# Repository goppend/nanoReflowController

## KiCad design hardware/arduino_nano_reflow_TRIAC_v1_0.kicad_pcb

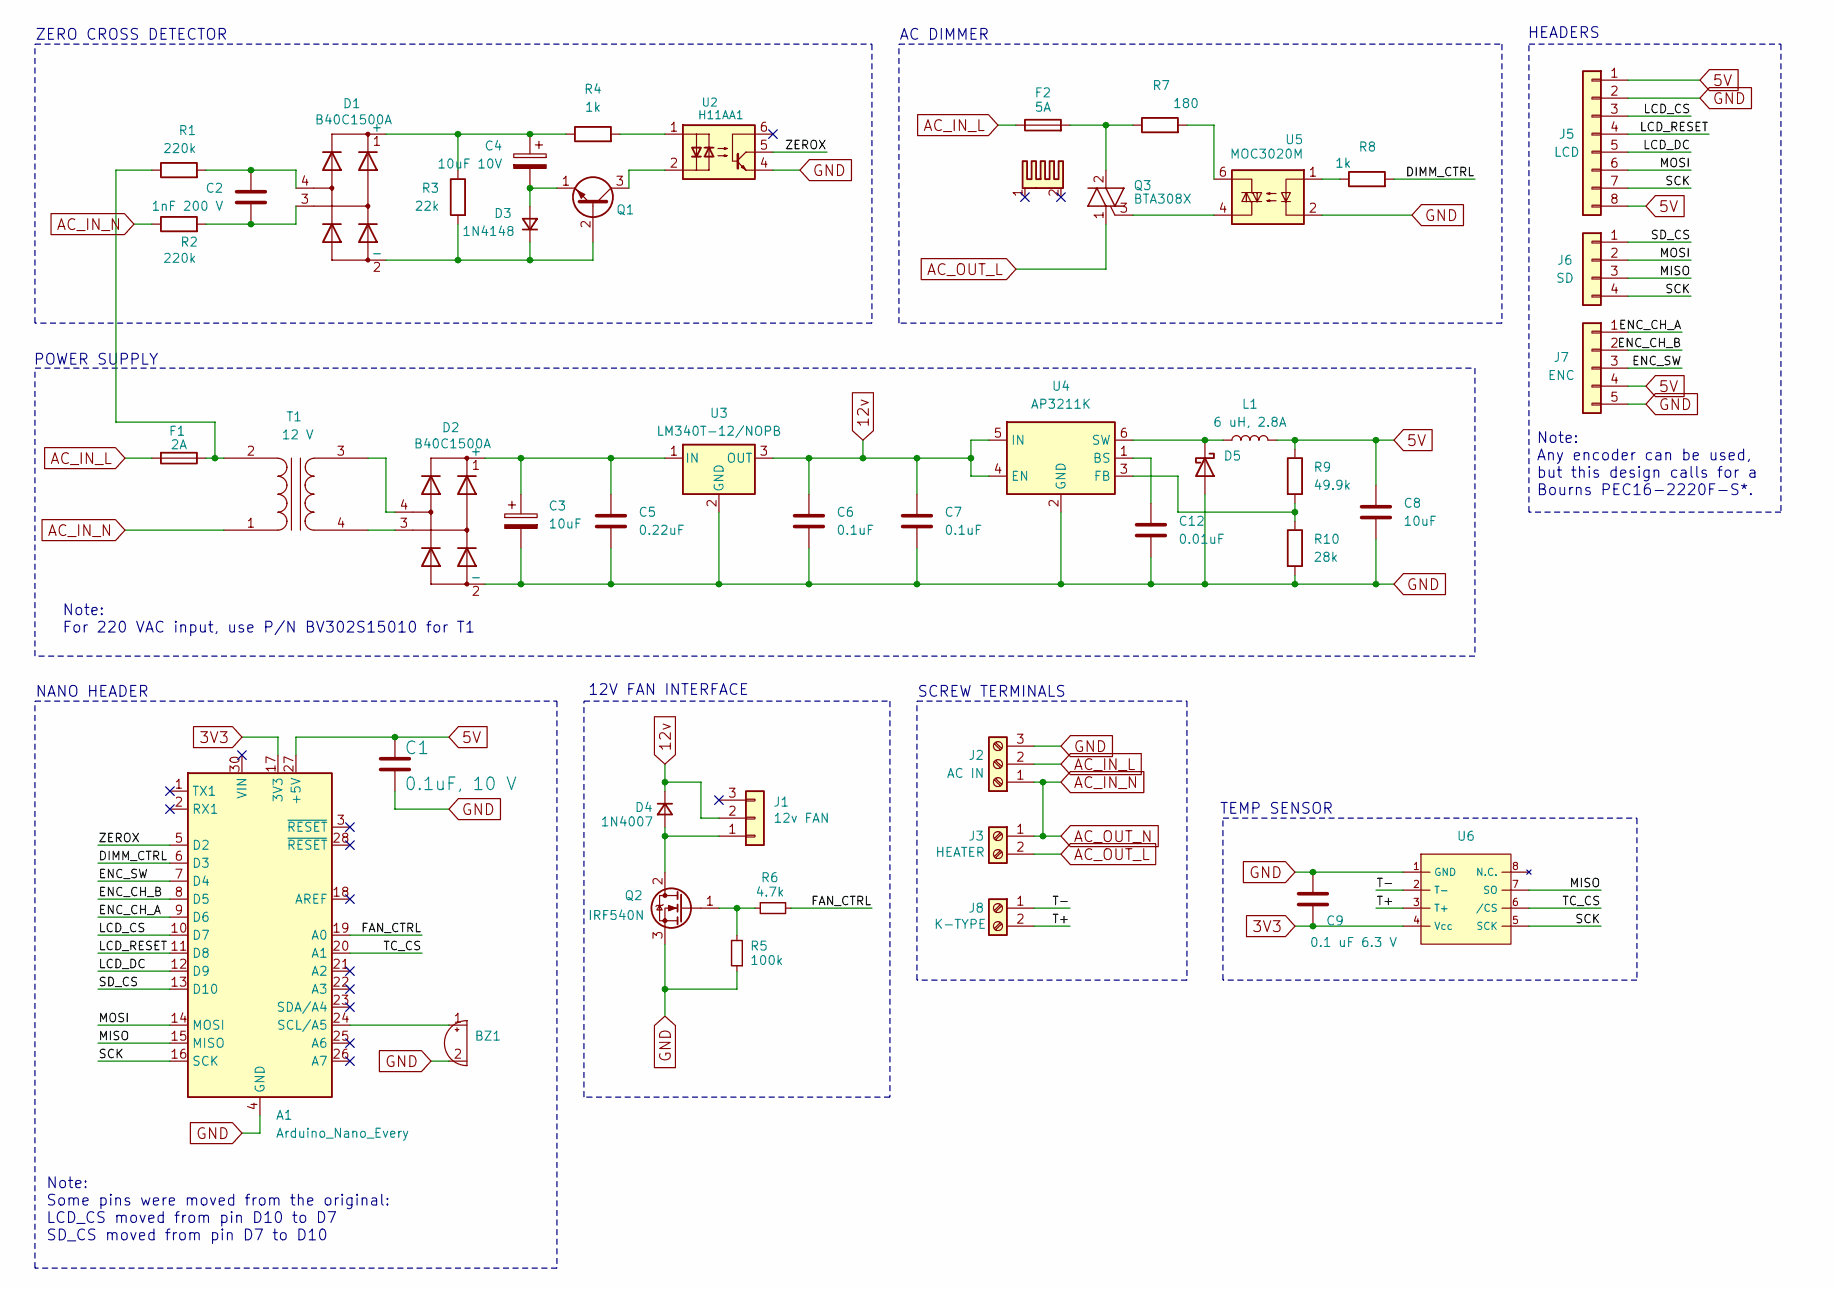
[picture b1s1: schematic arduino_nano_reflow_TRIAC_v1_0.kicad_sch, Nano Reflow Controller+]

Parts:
A1: Arduino_Nano_Every; Arduino_Nano
BZ1: Buzzer_TDK_PS1240P02BT_D12.2mm_H6.5mm; Part Number WT-1205
C1: 0.1uF, 10 V; C_0805_2012Metric_Pad1.18x1.45mm_HandSolder; Part Number C0805C104K8RACTU
C2: 1nF 200 V; C_Rect_L7.2mm_W2.5mm_P5.00mm_FKS2_FKP2_MKS2_MKP2; Part Number R82MC1100DQ50K
C3: 10uF; CP_Radial_D5.0mm_P2.00mm; Part Number ESS106M025AB2AA
C4: 10uF 10V; CP_Radial_D5.0mm_P2.00mm; Part Number ESK106M010AC3AA
C5: 0.22uF; C_0805_2012Metric_Pad1.18x1.45mm_HandSolder; Part Number C0805C224MMREC7210
C6, C7: 0.1uF; C_0805_2012Metric_Pad1.18x1.45mm_HandSolder; Part Number C0805C104K3RACTU
C8: 10uF; C_0805_2012Metric_Pad1.18x1.45mm_HandSolder; Part Number C0805C106K9PACTU
C9: 0.1 uF 6.3 V; C_0805_2012Metric_Pad1.18x1.45mm_HandSolder; Part Number C0805C104K9RACTU
C12: 0.01uF; C_0805_2012Metric_Pad1.18x1.45mm_HandSolder; Part Number C0805C103K8RACTU
D1, D2: B40C1500A; B40C; Part Number B40C1500A
D3: 1N4148; D_DO-35_SOD27_P7.62mm_Horizontal; Part Number 1N4148
D4: 1N4007; D_DO-35_SOD27_P7.62mm_Horizontal; Part Number 1N4007
D5: 40V, 2A; D_SMA_Handsoldering; Part Number B240A-13-F
F1: 2A; FUSE_0PTF0078P_LTF; Part Number 0PTF0078P
F2: 5A; FUSE_0PTF0078P_LTF; Part Number 0PTF0078P
HS1: Aavid 51300 Heatsink; Part Number 513102B02500G
J1: 12v FAN; FanPinHeader_1x03_P2.54mm_Vertical; Part Number 640456-3
J2: AC IN; TerminalBlock_Phoenix_MKDS-1,5-3_1x03_P5.00mm_Horizontal; Part Number 1727023
J3: HEATER; TerminalBlock_Phoenix_MKDS-1,5-2_1x02_P5.00mm_Horizontal; Part Number 1727010
J5: LCD; PinHeader_1x08_P2.54mm_Vertical; Part Number M20-9990846
J6: SD; PinHeader_1x04_P2.54mm_Vertical; Part Number M20-9990546
J7: ENC; PinHeader_1x05_P2.54mm_Vertical; Part Number M20-9990546
J8: K-TYPE; TerminalBlock_Phoenix_MKDS-1,5-2_1x02_P5.00mm_Horizontal; Part Number 1727010
L1: 6 uH, 2.8A; Bourns SRN6028C Inductor hand solder; Part Number SRN6028C-6R0M
Q1: 40V, 0.8A; TO-92_Inline_Wide; Part Number PN2222A PBFREE
Q2: IRF540N; TO-220-3_Vertical; Part Number IRF540N
Q3: BTA308X; TO-220-3_Vertical; Part Number BTA308X
R1, R2: 220k; R_Axial_DIN0204_L3.6mm_D1.6mm_P5.08mm_Horizontal; Part Number CF18JT220K
R3: 22k; R_Axial_DIN0204_L3.6mm_D1.6mm_P5.08mm_Horizontal; Part Number CF18JT22K0
R4, R8: 1k; R_Axial_DIN0204_L3.6mm_D1.6mm_P5.08mm_Horizontal; Part Number CF18JT1K00
R5: 100k; R_Axial_DIN0204_L3.6mm_D1.6mm_P5.08mm_Horizontal; Part Number CF18JT100K
R6: 4.7k; R_Axial_DIN0204_L3.6mm_D1.6mm_P5.08mm_Horizontal; Part Number CF18JT4K70
R7: 180; R_Axial_DIN0207_L6.3mm_D2.5mm_P7.62mm_Horizontal; Part Number CF18JT180R
R9: 49.9k; R_0805_2012Metric_Pad1.20x1.40mm_HandSolder; Part Number RK73H2ATTD4992F
R10: 28k; R_0805_2012Metric_Pad1.20x1.40mm_HandSolder; Part Number RK73H2ATTD2802F
T1: 12 V; BV301S15010; Part Number BV301S15010
U2: H11AA1; DIP-6_W7.62mm; Part Number H11AA1
U3: LM340T-12/NOPB; TO-263-3_TabPin4; Part Number LM340T-12/NOPB
U4: AP3211K; SOT-23-6_Handsoldering; Part Number AP3211K
U5: MOC3020M; DIP-6_W7.62mm_Socket_LongPads; Part Number MOC3020M
U6: SO-8_3.9x4.9mm_P1.27mm; Part Number MAX6675

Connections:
3V3: A1.17 (3V3), C9.2, U6.4 (Vcc)
5V: A1.27 (+5V), C1.1, C8.1, J5.1, J5.8, J7.4, L1.2, R9.1
12v: C6.1, C7.1, D4.1 (K), J1.2, U3.3 (OUT), U4.4 (EN), U4.5 (IN)
/DIMM_CTRL: A1.6 (D3), R8.2
/ENC_CH_A: A1.9 (D6), J7.1
/ENC_CH_B: A1.8 (D5), J7.2
/ENC_SW: A1.7 (D4), J7.3
/FAN_CTRL: A1.19 (A0), R6.1
/LCD_CS: A1.10 (D7), J5.3
/LCD_DC: A1.12 (D9), J5.5
/LCD_RESET: A1.11 (D8), J5.4
/MISO: A1.15 (MISO), J6.3, U6.7 (SO)
/MOSI: A1.14 (MOSI), J5.6, J6.2
/SCK: A1.16 (SCK), J5.7, J6.4, U6.5 (SCK)
/SD_CS: A1.13 (D10), J6.1
/T+: J8.2, U6.3 (T+)
/T-: J8.1, U6.2 (T-)
/TC_CS: A1.20 (A1), U6.6 (/CS)
/ZEROX: A1.5 (D2), U2.5
AC_IN_L: F1.2, F2.1, J2.2
AC_IN_N: J2.1, J3.1, R2.1, T1.1 (AA)
AC_OUT_L: J3.2, Q3.1 (A1)
GND: A1.4 (GND), A1.29 (GND), BZ1.2 (+), C1.2, C3.2, C5.2, C6.2, C7.2, C8.2, C9.1, C12.2, D2.2 (-), D5.2 (A), J2.3, J5.2, J7.5, Q2.3 (S), R5.1, R10.2, U2.4, U3.2 (GND), U4.2 (GND), U5.2, U6.1 (GND)
unnamed: A1.24 (SCL/A5), BZ1.1 (-)
unnamed: C2.1, D1.4, R1.2
unnamed: C2.2, D1.3, R2.2
unnamed: C4.1, D1.1 (+), R3.1, R4.1
unnamed: D1.2 (-), D3.1 (K), Q1.2 (B), R3.2
unnamed: C3.1, C5.1, D2.1 (+), U3.1 (IN)
unnamed: C4.2, D3.2 (A), Q1.1 (E)
unnamed: D4.2 (A), J1.1, Q2.2 (D)
unnamed: D5.1 (K), L1.1, U4.6 (SW)
unnamed: Q1.3 (C), U2.2
unnamed: Q2.1 (G), R5.2, R6.2
unnamed: F2.2, Q3.2 (A2), R7.1
unnamed: Q3.3 (G), U5.4
unnamed: R4.2, U2.1
unnamed: R7.2, U5.6
unnamed: R8.1, U5.1
unnamed: F1.1, R1.1, T1.2 (AB)
unnamed: D2.4, T1.3 (SA)
unnamed: D2.3, T1.4 (SB)
unnamed: C12.1, U4.1 (BS)
unnamed: R9.2, R10.1, U4.3 (FB)

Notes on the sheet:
AC DIMMER
ZERO CROSS DETECTOR
Note: Any encoder can be used, but this design calls for a Bourns PEC16-2220F-S*.
HEADERS
Note: Some pins were moved from the original: LCD_CS moved from pin D10 to D7 SD_CS moved from pin D7 to D10
SCREW TERMINALS
TEMP SENSOR
Note: For 220 VAC input, use P/N BV302S15010 for T1
POWER SUPPLY
NANO HEADER
12V FAN INTERFACE

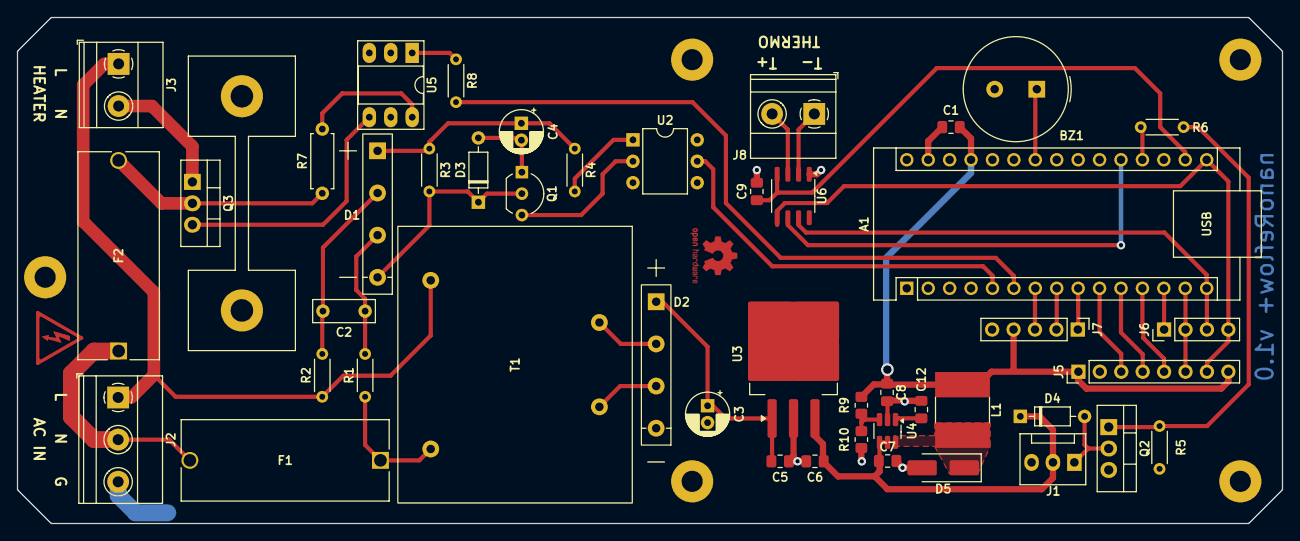
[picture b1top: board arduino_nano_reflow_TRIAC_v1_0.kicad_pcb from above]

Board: 2 copper layers, 150.0 x 60.0 mm, 47 parts (0 on the bottom side), 44 nets.

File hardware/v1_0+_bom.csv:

#,Reference,Qty,Description,Value,Manufacturer,Part Number
1,BZ1,1,Buzzer,,Same Sky,CEM-1205-IC
2,C1,1,Ceramic Capacitor,"0.1uF, 10 V",Kemet,C0805C104K8RACTU
3,C2,1,Poly Film Capacitor,1nF 200 V,Kemet,R82MC1100DQ50K
4,C3,1,Aluminum Electrolytic Capacitor,10uF,Kemet,ESS106M025AB2AA
5,C4,1,Aluminum Electrolytic Capacitor,10uF 10V,Kemet,ESK106M010AC3AA
6,C5,1,Ceramic Capacitor,0.22uF,Kemet,C0805C224MMREC7210
7,C6,1,Ceramic Capacitor,0.1uF,Kemet,C0805C104K3RACTU
8,C7,1,Ceramic Capacitor,0.1uF,Kemet,C0805C104K3RACTU
9,C8,1,Ceramic Capacitor,10uF,Kemet,C0805C106K9PACTU
10,C9,1,Ceramic Capacitor,0.1 uF 6.3 V,Kemet,C0805C104K9RACTU
11,C12,1,Ceramic Capacitor,0.01uF,Kemet,C0805C103K8RACTU
12,D1,1,Bridge Rectifier,B40C1500A,Diotec,B40C1500A
13,D2,1,Bridge Rectifier,B40C1500A,Diotec,B40C1500A
14,D3,1,"Diode, signal",1N4148,ON Semi,1N4148
15,D4,1,"Diode, rectifier",1N4007,Diotec,1N4007
16,D5,1,Schottky diode,"40V, 2A",Diodes Inc,B240A-13-F
17,F1,1,Fuse Holder,2A,Littelfuse,0PTF0078P
18,F2,1,Fuse Holder,5A,Littelfuse,0PTF0078P
19,HS1,1,Heatsink,,Bivar/Aavid,513102B02500G
20,J1,1,Fan Header,12v FAN,TE Connectivity,640456-3
21,J2,1,"Screw Terminal Block, 3 position",AC IN,Phoenix,1727023
22,J3,1,"Screw Terminal Block, 2 position",HEATER,Phoenix,1727010
23,"U2, U5",2,"Socket, 6-DIP",,Mill-Max,110-44-306-41-001000
24,U1,1,"Socket, 28-DIP",,Assmann WSW,A 28-LC-TT 
25,J8,1,"Screw Terminal Block, 2 position",K-TYPE,Phoenix,1727010
26,L1,1,Inductor,"6 uH, 2.8A",Bourns,SRN6028C-6R0M
27,Q1,1,"Transistor, NPN","40V, 0.8A",Central Semi,PN2222A PBFREE
28,Q2,1,"Mosfet, N-Channel",IRF540N,International Rectifier,IRF540N
29,Q3,1,Triac,BTA308X,WeEn Semiconductor,BTA308X
30,R1,1,Resistor,220k,Stackpole,CF18JT220K
31,R2,1,Resistor,220k,Stackpole,CF18JT220K
32,R3,1,Resistor,22k,Stackpole,CF18JT22K0
33,R4,1,Resistor,1k,Stackpole,CF18JT1K00
34,R5,1,Resistor,100k,Stackpole,CF18JT100K
35,R6,1,Resistor,4.7k,Stackpole,CF18JT4K70
36,R7,1,Resistor,180,Stackpole,CF18JT180R
37,R8,1,Resistor,1k,Stackpole,CF18JT1K00
38,R9,1,Resistor,49.9k,KOA Speer,RK73H2ATTD4992F
39,R10,1,Resistor,28k,KOA Speer,RK73H2ATTD2802F
40,T1,1,Transformer,12 V,Zettler Magnetics,BV301S15010
41,S1,1,Rotary Encoder,,Bourns,PEC16-2220F-S0024
42,U2,1,"AC/DC NPN Optocoupler, DIP-6",H11AA1,Vishay,H11AA1
43,U3,1,Positive 1.5A 35V Linear Regulator,LM340T-12/NOPB,Texas Instruments,LM340T-12/NOPB
44,U4,1,"1.5A, Adjustable Step-Down Voltage Regulator",AP3211K,"Diodes, Inc",AP3211K
45,U5,1,"Random Phase Opto-Triac, Vdrm 400V, Ift 30mA",MOC3020M,ON Semiconductor,MOC3020M
46,U6,1,Type-K Thermocouple to Digital Interface,,Analog Devices,MAX6675

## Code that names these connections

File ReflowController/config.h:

#ifndef CONFIG_H
#define CONFIG_H

//#define ALWAYS_FIRST_RUN // force resett to factory settings at startup
//#define FAKE_HW 1
//#define PIDTUNE 1 // autotune wouldn't fit in the 28k available on my arduino pro micro.
#define WITH_BEEPER // Enables Beeper
//#define WITH_FAN // Enables Lid opening Servo (not yet implemented)
//#define WITH_SERVO // Enables Lid opening Servo (not yet implemented)
//#define SERIAL_VERBOSE


// ----------------------------------------------------------------------------

#define WITH_SPLASH 1


static const uint8_t PIN_LCD_CS   = 10;
static const uint8_t PIN_LCD_DC   = 9;
static const uint8_t PIN_LCD_RST  = 8;
static const uint8_t LCD_ROTATION = 3; // 0/2-> portrait, 1/3-> landscape

static const uint8_t PIN_TC_CS   = A1;
static const uint8_t PIN_TC_DO   = 12;
static const uint8_t PIN_TC_CLK  = 13;
static const uint8_t PIN_HEATER = 3; // 
static const uint8_t PIN_FAN    = A0; // 
static const uint8_t PIN_BEEPER = A5; // Beeper Out
// --- encoder
static const uint8_t PIN_ENC_A           = A2; // 
static const uint8_t PIN_ENC_B           = A3; // 
static const uint8_t PIN_ENC_BTN         = A4; // 
static const uint8_t ENC_STEPS_PER_NOTCH = 4;
static const boolean IS_ENC_ACTIVE       = false; // encoder module actively fed with VCC ( seems to works bad if set to true )

static const uint16_t BEEP_FREQ = 1976; // B6 note

static const uint8_t PIN_ZX = 2; // pin for zero crossing detector
static const uint8_t INT_ZX = digitalPinToInterrupt(PIN_ZX); // interrupt for zero crossing detector

static const uint8_t NUM_TEMP_READINGS  = 5;
static const uint8_t TC_ERROR_TOLERANCE = 5; // allow for n consecutive errors due to noisy power supply before bailing out
static const float   TEMP_COMPENSATION  = 1.0; // correction factor to match temperature measured with other device



// see: https://www.compuphase.com/electronics/reflowsolderprofiles.htm  
static const uint8_t DEFAULT_SOAK_TEPM_A      = 110;
static const uint8_t DEFAULT_SOAK_TEPM_B      = 160; 
static const uint8_t DEFAULT_SOAK_DURATION    = 180; 
static const uint8_t DEFAULT_PEAK_TEPM        = 200;
static const uint8_t DEFAULT_PEAK_DURATION    = 15;
static const float DEFAULT_RAMP_UP_RATE       = 1.2; // degrees / second (keep it about 1/2 of maximum to prevent PID overshooting)
static const float DEFAULT_RAMP_DOWN_RATE     = 2.0; // degrees / second
static const uint8_t FACTORY_FAN_ASSIST_SPEED = 33;


/*
Kp: Determines how aggressively the PID reacts to the current amount of error (Proportional) (double >=0)
Ki: Determines how aggressively the PID reacts to error over time (Integral) (double>=0)
Kd: Determines how aggressively the PID reacts to the change in error (Derivative) (double>=0)

Experimental method to tune PID:

> Set all gains to 0.
> Increase Kd until the system oscillates.
> Reduce Kd by a factor of 2-4.
> Set Kp to about 1% of Kd.
> Increase Kp until oscillations start.
> Decrease Kp by a factor of 2-4.
> Set Ki to about 1% of Kp.
> Increase Ki until oscillations start.
> Decrease Ki by a factor of 2-4.

*/
#define PID_SAMPLE_TIME 200
#define FACTORY_KP  1.75 // 1.75 //4.0 
#define FACTORY_KI 0.03 // 0.03 // 0.05 
#define FACTORY_KD 3.0 //3.0//2.0 





#endif // CONFIG_H

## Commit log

2019-07-02 add TimerOne submodule
2019-11-09 Auto calibrate mains freq and loop delay, reduce TIMER1_PERIOD_US
2019-11-09 add PID_AutoTune_v0 submodule
2019-11-09 cleanup
2019-11-09 change comment
2025-01-12 Extract project to track changes and update to KiCad 8
2025-01-13 Update schematic: Reorganized and added AC power supply.
2025-01-18 Big update. Lots of schematic reorg and mostly final PCB layout. Updated zero crossing detector to be more accurate and added temp sensor on board instead of a connector to a separate module. Moved s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
2025-01-18 Some small changes I forgot in the last commit, and an updated BOM.
2025-01-18 Fixed grid in PCB, minor movement changes, and fixed DRC issues.
